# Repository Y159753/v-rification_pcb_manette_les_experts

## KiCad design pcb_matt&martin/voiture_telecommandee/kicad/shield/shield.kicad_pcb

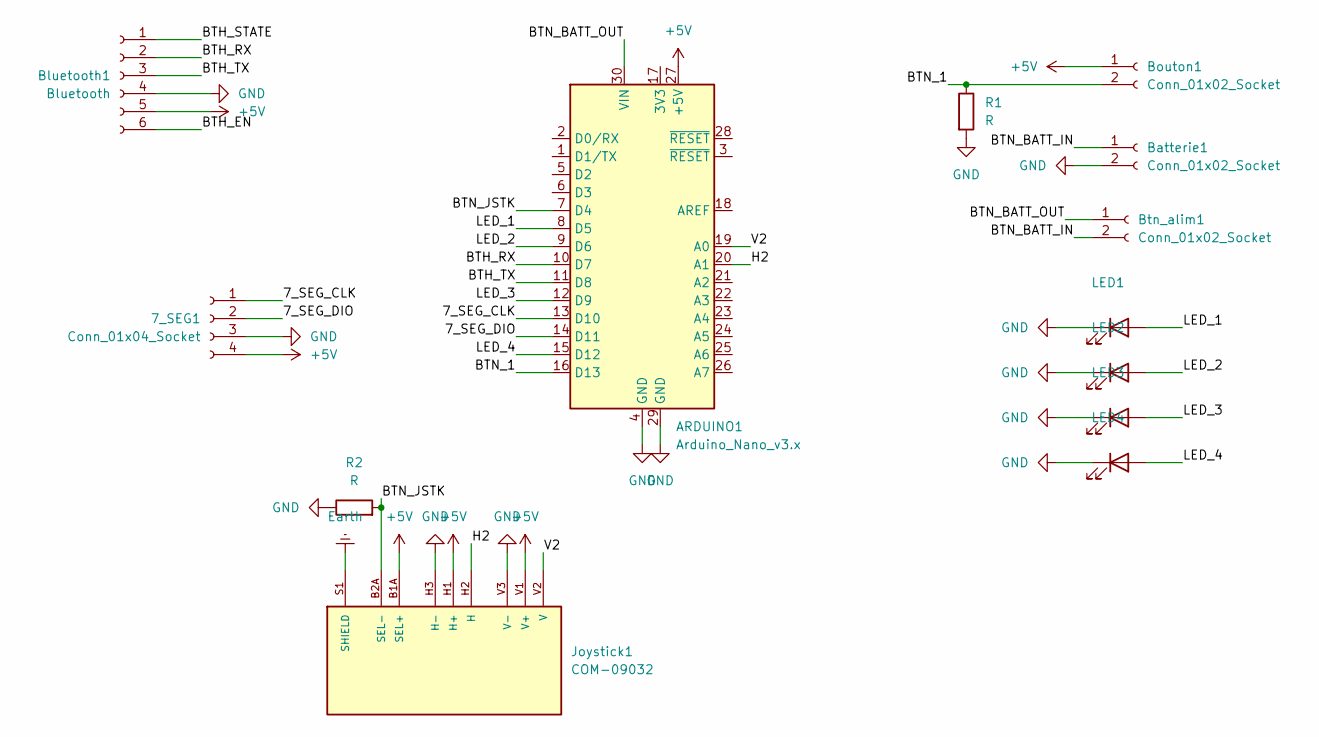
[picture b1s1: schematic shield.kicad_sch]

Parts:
7_SEG1: Conn_01x04_Socket; PinSocket_1x04_P2.54mm_Vertical
ARDUINO1: Arduino_Nano_v3.x; Arduino_Nano
Batterie1: Conn_01x02_Socket; JST_XH_B2B-XH-A_1x02_P2.50mm_Vertical
Bluetooth1: Bluetooth; PinSocket_1x06_P2.54mm_Horizontal
Bouton1: Conn_01x02_Socket; JST_XH_B2B-XH-A_1x02_P2.50mm_Vertical
Btn_alim1: Conn_01x02_Socket; JST_XH_B2B-XH-A_1x02_P2.50mm_Vertical
Joystick1: COM-09032; XDCR_COM-09032; PARTREV N/A
LED1, LED2, LED3, LED4: LED; LED_D5.0mm_Clear
R1, R2: R; R_Axial_DIN0207_L6.3mm_D2.5mm_P10.16mm_Horizontal

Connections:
+5V: 7_SEG1.4, ARDUINO1.27 (+5V), Bluetooth1.5, Bouton1.1, Joystick1.B1A (SEL+), Joystick1.H1 (H+), Joystick1.V1 (V+)
/7_SEG_CLK: 7_SEG1.1, ARDUINO1.13 (D10)
/7_SEG_DIO: 7_SEG1.2, ARDUINO1.14 (D11)
/<NO NET>: ARDUINO1.7 (D4), Joystick1.B2A (SEL-), R2.2
/BTH_EN: Bluetooth1.6
/BTH_RX: ARDUINO1.10 (D7), Bluetooth1.2
/BTH_STATE: Bluetooth1.1
/BTH_TX: ARDUINO1.11 (D8), Bluetooth1.3
/BTN_1: ARDUINO1.16 (D13), Bouton1.2, R1.1
/BTN_BATT_IN: Batterie1.1, Btn_alim1.2
/BTN_BATT_OUT: ARDUINO1.30 (VIN), Btn_alim1.1
/H2: ARDUINO1.20 (A1), Joystick1.H2 (H)
/LED_1: ARDUINO1.8 (D5), LED1.2 (A)
/LED_2: ARDUINO1.9 (D6), LED2.2 (A)
/LED_3: ARDUINO1.12 (D9), LED3.2 (A)
/LED_4: ARDUINO1.15 (D12), LED4.2 (A)
/V2: ARDUINO1.19 (A0), Joystick1.V2 (V)
Earth: Joystick1.S1 (SHIELD), Joystick1.S2 (SHIELD), Joystick1.S3 (SHIELD), Joystick1.S4 (SHIELD)
GND: 7_SEG1.3, ARDUINO1.4 (GND), ARDUINO1.29 (GND), Batterie1.2, Bluetooth1.4, Joystick1.H3 (H-), Joystick1.V3 (V-), LED1.1 (K), LED2.1 (K), LED3.1 (K), LED4.1 (K), R1.2, R2.1

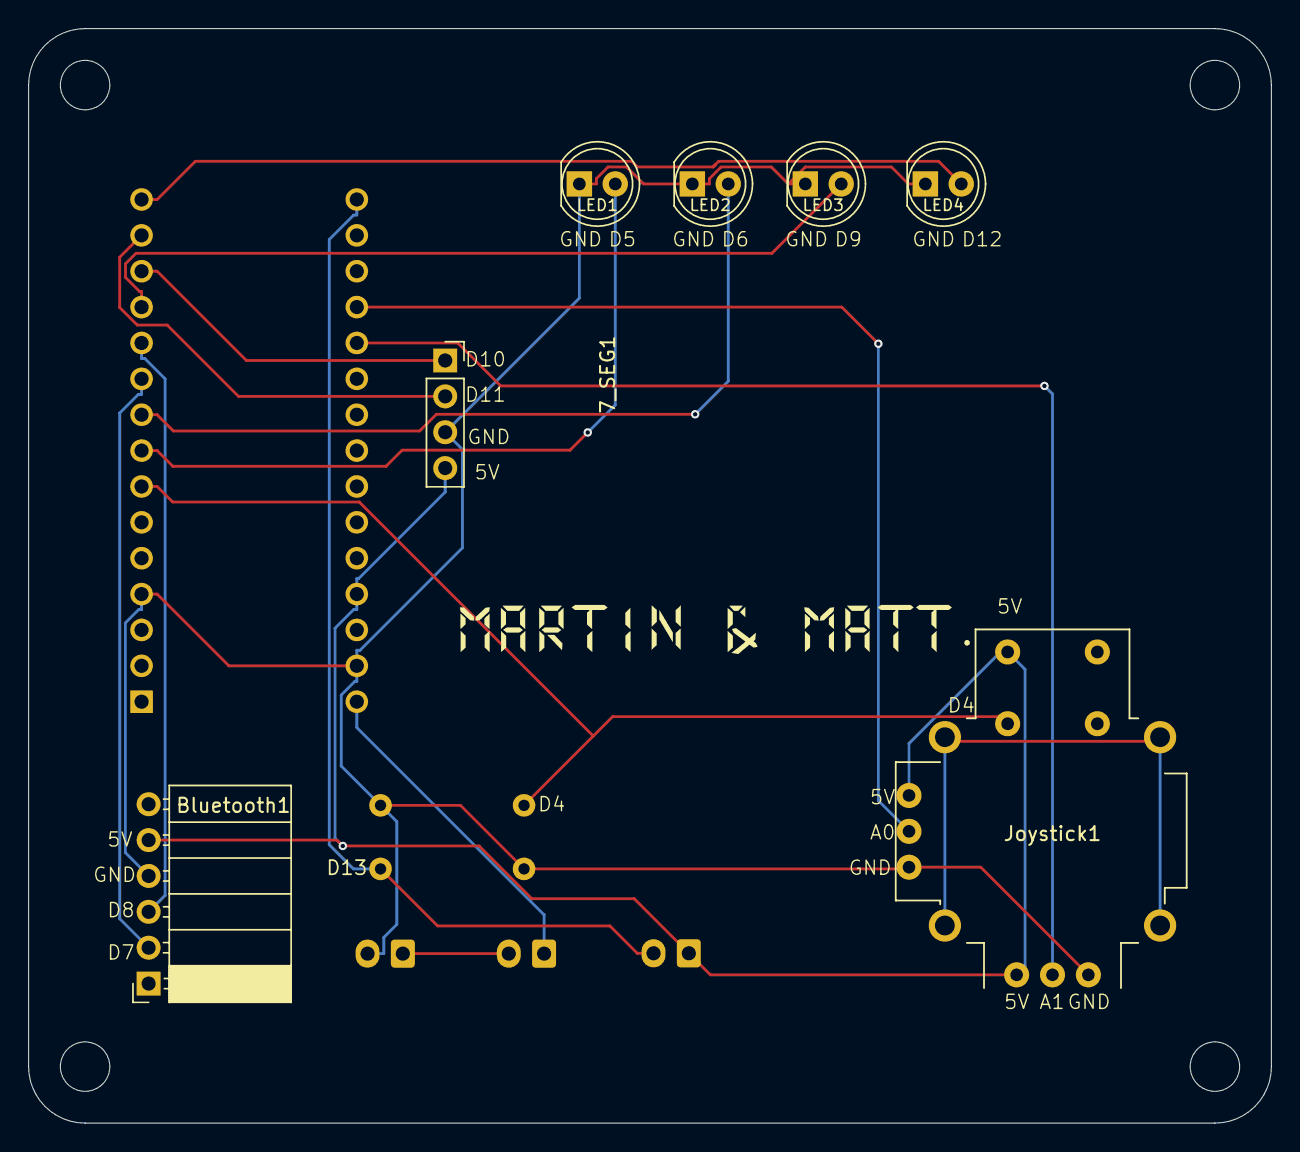
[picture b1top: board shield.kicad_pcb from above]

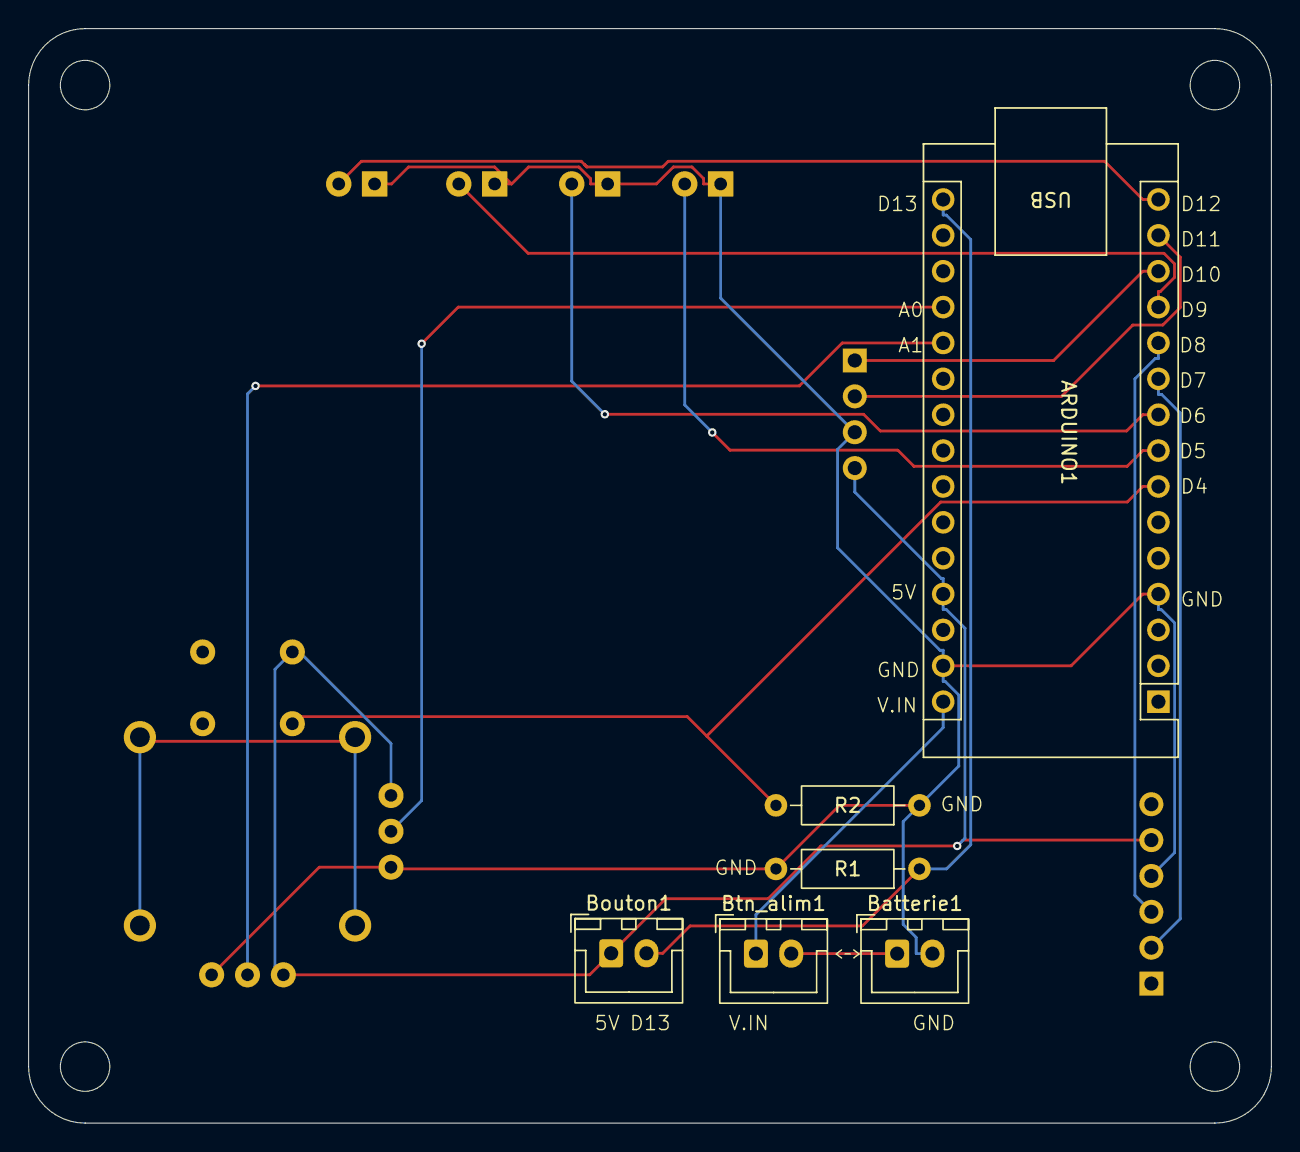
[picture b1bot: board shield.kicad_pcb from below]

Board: 2 copper layers, 88.0 x 77.5 mm, 13 parts (6 on the bottom side), 17 nets.

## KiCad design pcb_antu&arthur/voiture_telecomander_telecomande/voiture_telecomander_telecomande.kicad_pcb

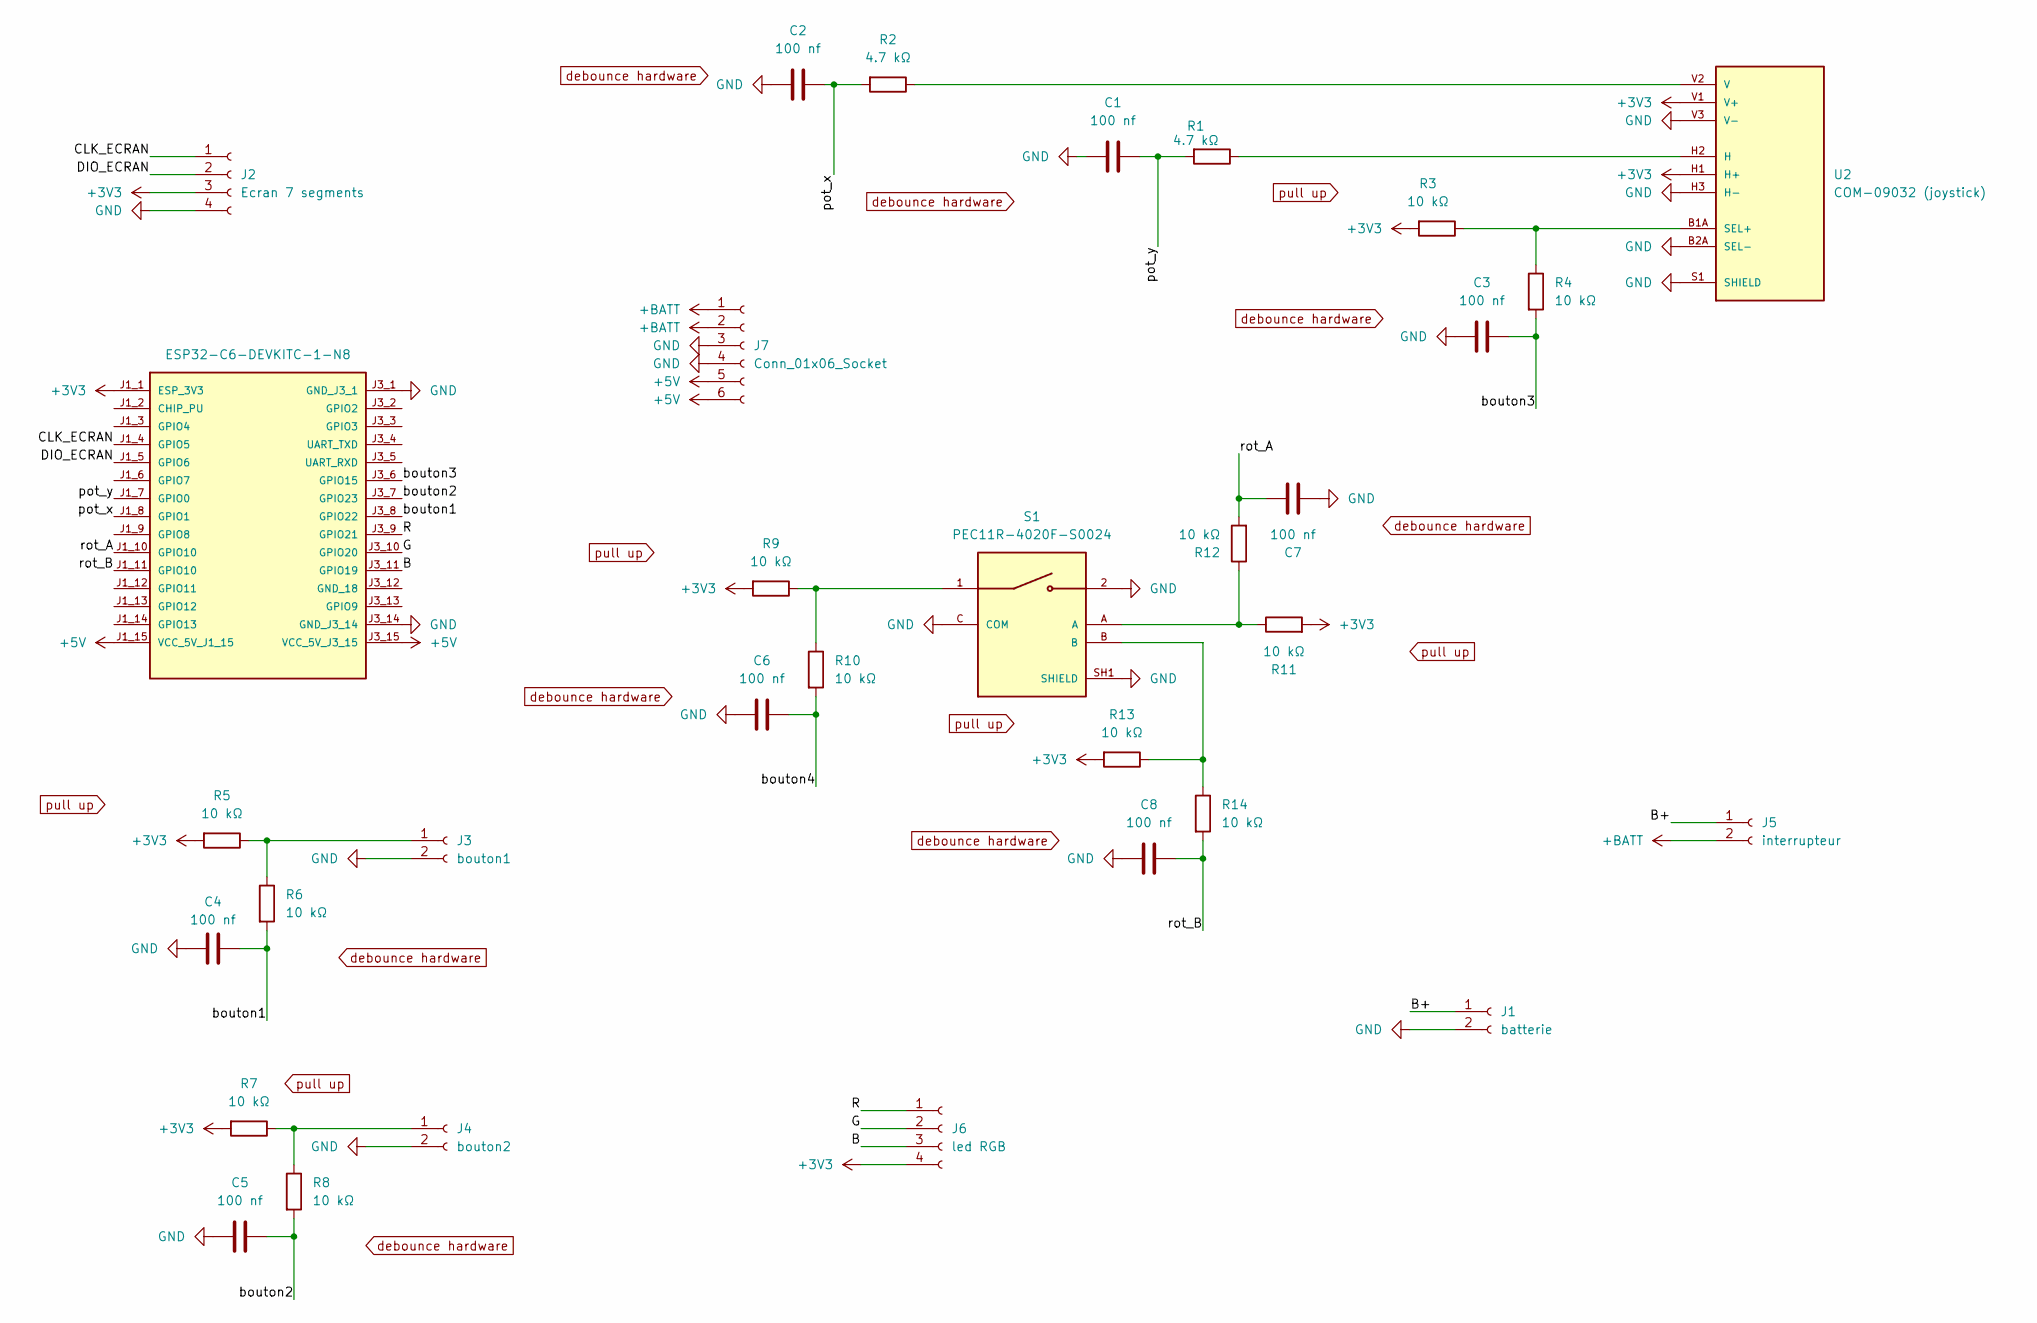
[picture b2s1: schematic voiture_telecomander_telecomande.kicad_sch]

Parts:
C1, C2, C3, C4, C5, C6, C7, C8: 100 nf; C_Radial_D4.0mm_H7.0mm_P1.50mm
J1: batterie; JST_XH_B2B-XH-A_1x02_P2.50mm_Vertical
J2: Ecran 7 segments; PinSocket_1x04_P2.54mm_Vertical
J3: bouton1; JST_XH_B2B-XH-A_1x02_P2.50mm_Vertical
J4: bouton2; JST_XH_B2B-XH-A_1x02_P2.50mm_Vertical
J5: interrupteur; JST_XH_B2B-XH-A_1x02_P2.50mm_Vertical
J6: led RGB; PinSocket_1x04_P2.54mm_Vertical
J7: Conn_01x06_Socket; PinSocket_1x06_P2.54mm_Vertical
R1, R2: 4.7 kΩ; R_Axial_DIN0207_L6.3mm_D2.5mm_P10.16mm_Horizontal
R3, R4, R5, R6, R7, R8, R9, R10, R11, R12, R13, R14: 10 kΩ; R_Axial_DIN0207_L6.3mm_D2.5mm_P10.16mm_Horizontal
S1: PEC11R-4020F-S0024; XDCR_PEC11R-4020F-S0024; PARTREV 11/23
U1: ESP32-C6-DEVKITC-1-N8; MODULE_ESP32-C6-DEVKITC-1-N8; PARTREV 1.3
U2: COM-09032 (joystick); XDCR_COM-09032; PARTREV N/A

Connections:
+3V3: J2.3, J6.4, R3.2, R5.2, R7.2, R9.2, R11.2, R13.2, U1.J1_1 (ESP_3V3), U2.H1 (H+), U2.V1 (V+)
+5V: J7.5, J7.6, U1.J1_15 (VCC_5V_J1_15), U1.J3_15 (VCC_5V_J3_15)
+BATT: J5.2, J7.1, J7.2
/B: J6.3, U1.J3_11 (GPIO19)
/B+: J1.1, J5.1
/CLK_ECRAN: J2.1, U1.J1_4 (GPIO5)
/DIO_ECRAN: J2.2, U1.J1_5 (GPIO6)
/G: J6.2, U1.J3_10 (GPIO20)
/R: J6.1, U1.J3_9 (GPIO21)
/bouton1: C4.2, R6.2, U1.J3_8 (GPIO22)
/bouton2: C5.2, R8.2, U1.J3_7 (GPIO23)
/bouton3: C3.2, R4.2, U1.J3_6 (GPIO15)
/bouton4: C6.2, R10.2
/pot_x: C2.2, R2.2, U1.J1_8 (GPIO1)
/pot_y: C1.2, R1.2, U1.J1_7 (GPIO0)
/rot_A: C7.2, R12.2, U1.J1_10 (GPIO10)
/rot_B: C8.2, R14.2, U1.J1_11 (GPIO10)
GND: C1.1, C2.1, C3.1, C4.1, C5.1, C6.1, C7.1, C8.1, J1.2, J2.4, J3.2, J4.2, J7.3, J7.4, S1.2, S1.C (COM), S1.SH1 (SHIELD), S1.SH2 (SHIELD), U1.J3_1 (GND_J3_1), U1.J3_14 (GND_J3_14), U2.B2A (SEL-), U2.H3 (H-), U2.S1 (SHIELD), U2.S2 (SHIELD), U2.S3 (SHIELD), U2.S4 (SHIELD), U2.V3 (V-)
unnamed: J3.1, R5.1, R6.1
unnamed: J4.1, R7.1, R8.1
unnamed: R9.1, R10.1, S1.1
unnamed: R11.1, R12.1, S1.A
unnamed: R13.1, R14.1, S1.B
unnamed: R1.1, U2.H2 (H)
unnamed: R3.1, R4.1, U2.B1A (SEL+)
unnamed: R2.1, U2.V2 (V)

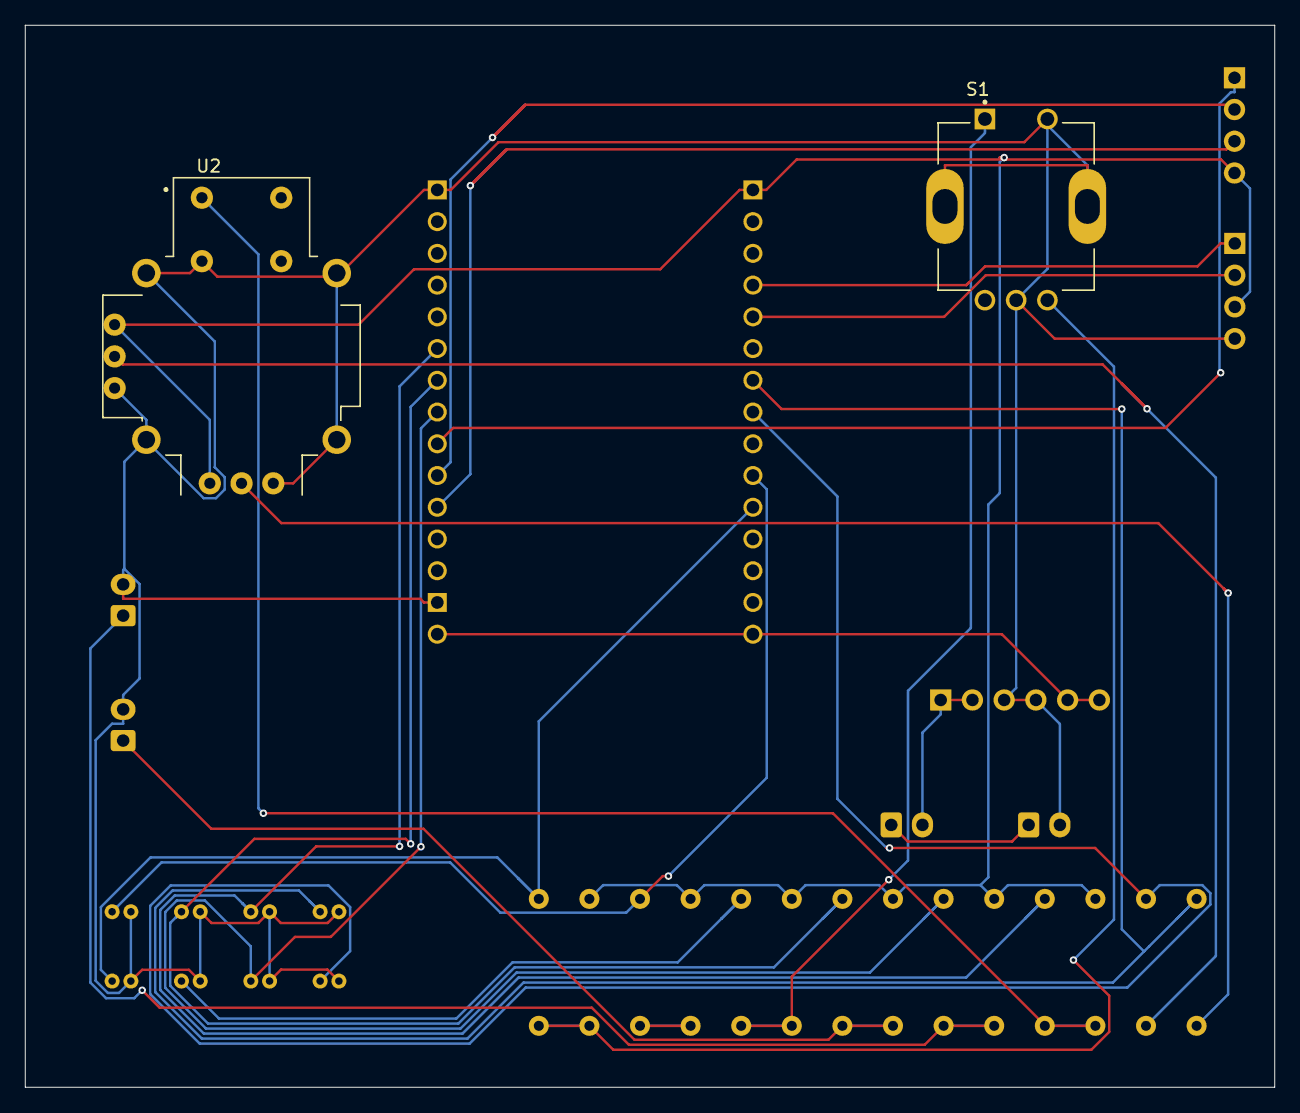
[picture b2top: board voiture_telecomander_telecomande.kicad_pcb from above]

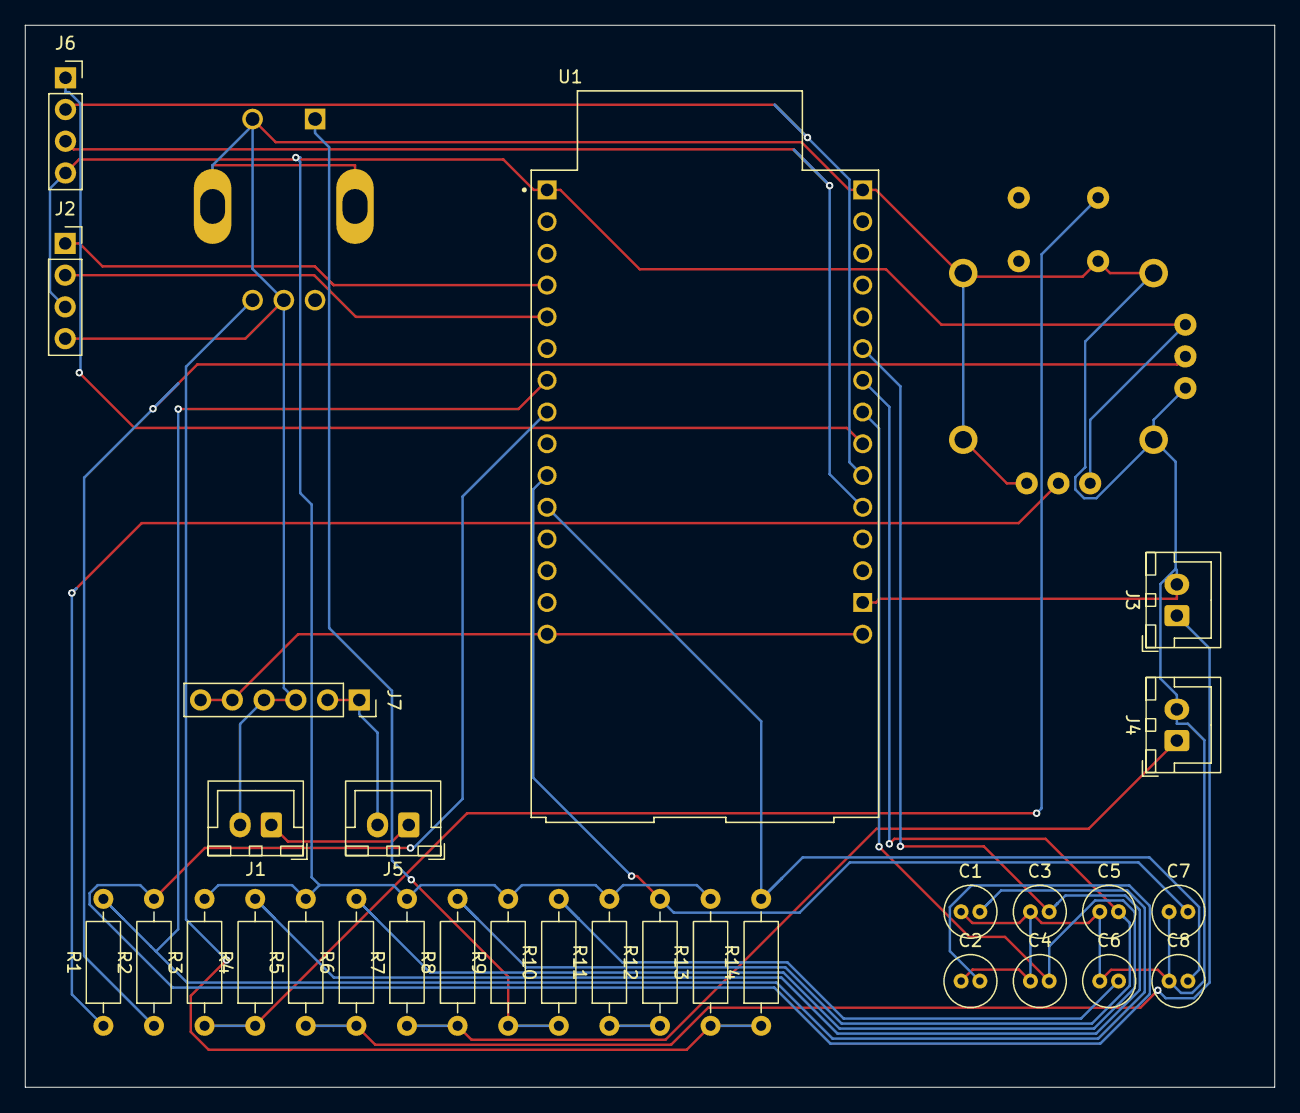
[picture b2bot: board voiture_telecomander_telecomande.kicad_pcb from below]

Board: 2 copper layers, 100.0 x 85.0 mm, 32 parts (30 on the bottom side), 26 nets.

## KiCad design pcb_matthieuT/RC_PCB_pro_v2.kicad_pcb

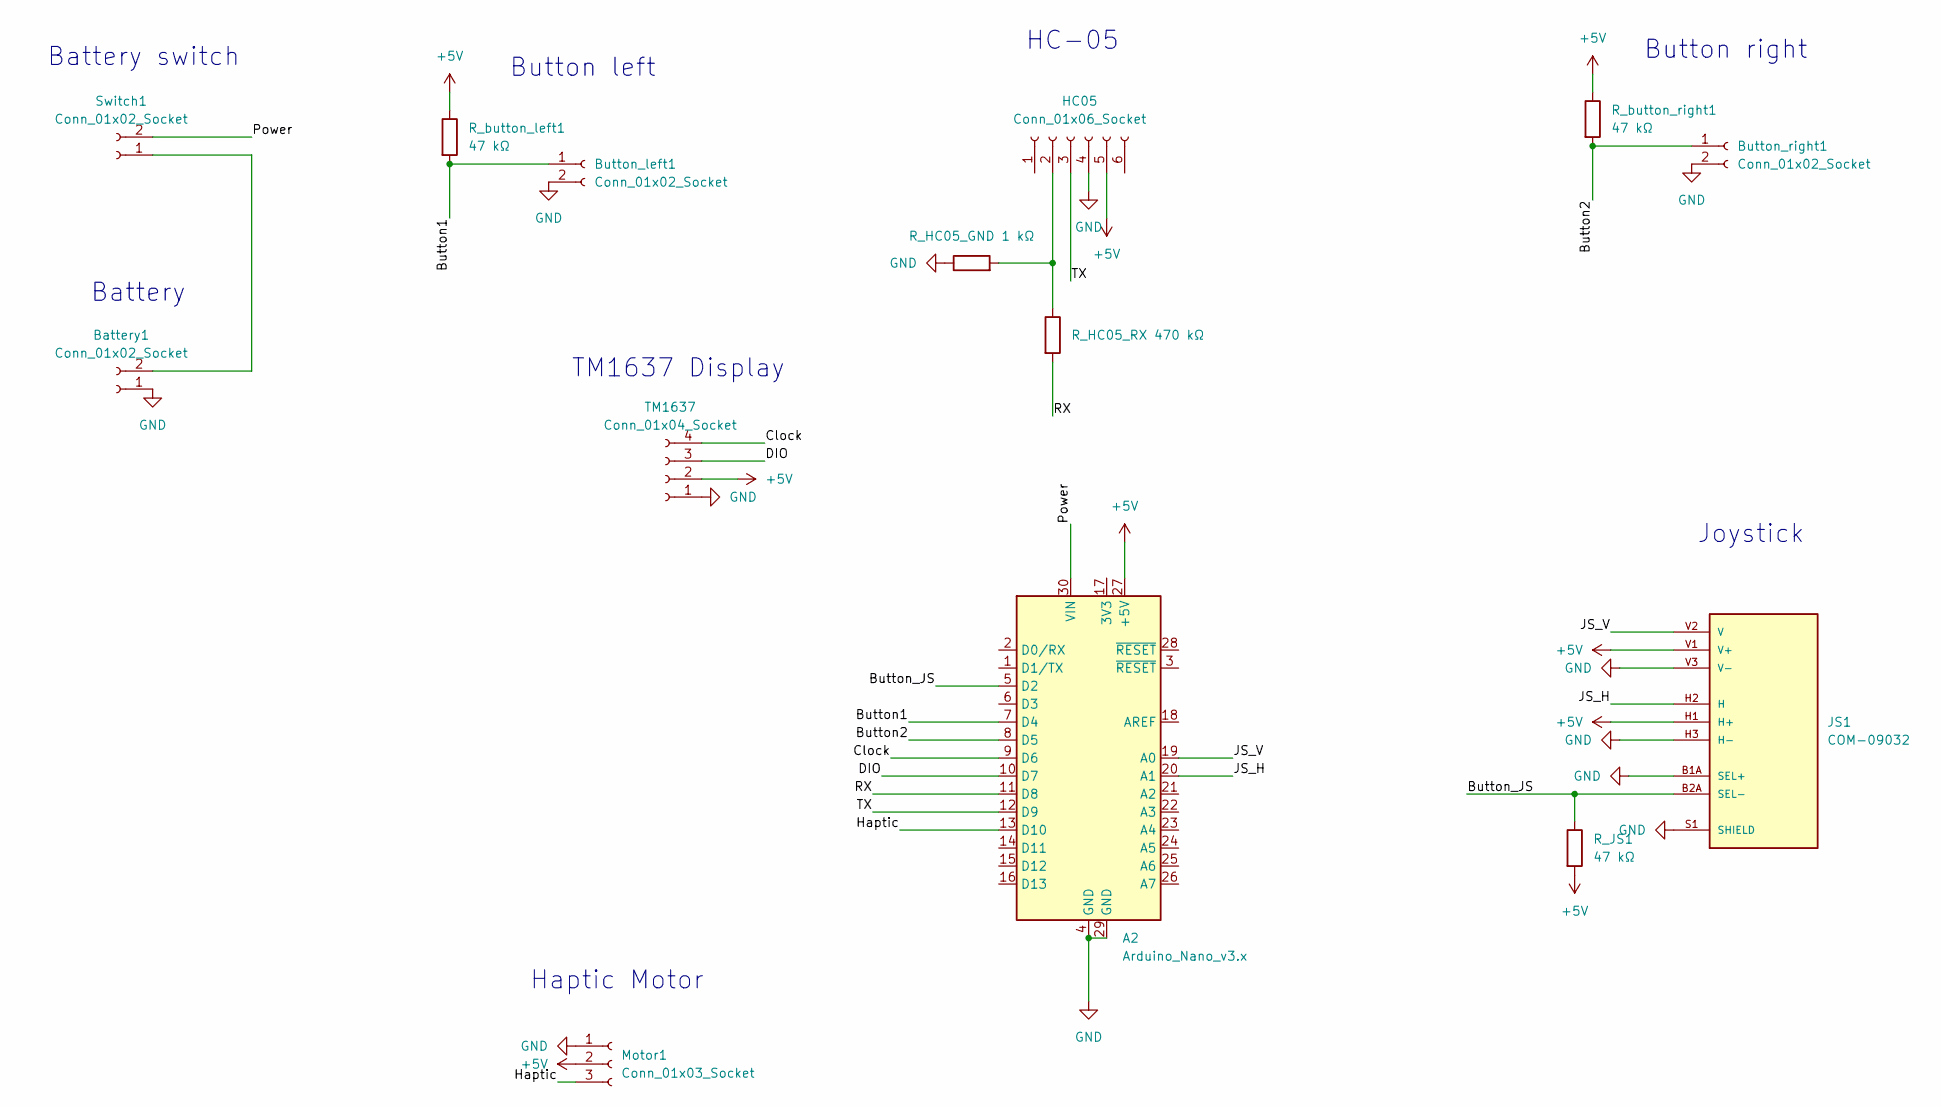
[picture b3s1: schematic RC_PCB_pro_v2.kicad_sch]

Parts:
A2: Arduino_Nano_v3.x; Arduino_Nano
Battery1: Conn_01x02_Socket; JST_XH_B2B-XH-A_1x02_P2.50mm_Vertical
Button_left1: Conn_01x02_Socket; JST_XH_B2B-XH-A_1x02_P2.50mm_Vertical
Button_right1: Conn_01x02_Socket; JST_XH_B2B-XH-A_1x02_P2.50mm_Vertical
HC05: Conn_01x06_Socket; PinSocket_1x06_P2.54mm_Horizontal
JS1: COM-09032; XDCR_COM-09032; PARTREV N/A
Motor1: Conn_01x03_Socket; PinSocket_1x03_P2.00mm_Horizontal
R1: R_HC05_RX 470 kΩ; R_Axial_DIN0207_L6.3mm_D2.5mm_P10.16mm_Horizontal
R2: R_HC05_GND 1 kΩ; R_Axial_DIN0207_L6.3mm_D2.5mm_P10.16mm_Horizontal
R_JS1: 47 kΩ; R_Axial_DIN0207_L6.3mm_D2.5mm_P10.16mm_Horizontal
R_button_left1: 47 kΩ; R_Axial_DIN0207_L6.3mm_D2.5mm_P10.16mm_Horizontal
R_button_right1: 47 kΩ; R_Axial_DIN0207_L6.3mm_D2.5mm_P10.16mm_Horizontal
Switch1: Conn_01x02_Socket; JST_XH_B2B-XH-A_1x02_P2.50mm_Vertical
TM1637: Conn_01x04_Socket; PinSocket_1x04_P2.54mm_Vertical

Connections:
+5V: A2.27 (+5V), HC05.5, JS1.H1 (H+), JS1.V1 (V+), Motor1.2, R_JS1.2, R_button_left1.1, R_button_right1.1, TM1637.2
/Button1: A2.7 (D4), Button_left1.1, R_button_left1.2
/Button2: A2.8 (D5), Button_right1.1, R_button_right1.2
/Button_JS: A2.5 (D2), JS1.B2A (SEL-), R_JS1.1
/Clock: A2.9 (D6), TM1637.4
/DIO: A2.10 (D7), TM1637.3
/Haptic: A2.13 (D10), Motor1.3
/JS_H: A2.20 (A1), JS1.H2 (H)
/JS_V: A2.19 (A0), JS1.V2 (V)
/Power: A2.30 (VIN), Switch1.2
/RX: A2.11 (D8), R1.2
/TX: A2.12 (D9), HC05.3
GND: A2.4 (GND), A2.29 (GND), Battery1.1, Button_left1.2, Button_right1.2, HC05.4, JS1.B1A (SEL+), JS1.H3 (H-), JS1.S1 (SHIELD), JS1.S2 (SHIELD), JS1.S3 (SHIELD), JS1.S4 (SHIELD), JS1.V3 (V-), Motor1.1, R2.1, TM1637.1
unnamed: Battery1.2, Switch1.1
unnamed: HC05.2, R1.1, R2.2

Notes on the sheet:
Battery
Battery switch
TM1637 Display
Button right
HC-05
Joystick
Haptic Motor
Button left

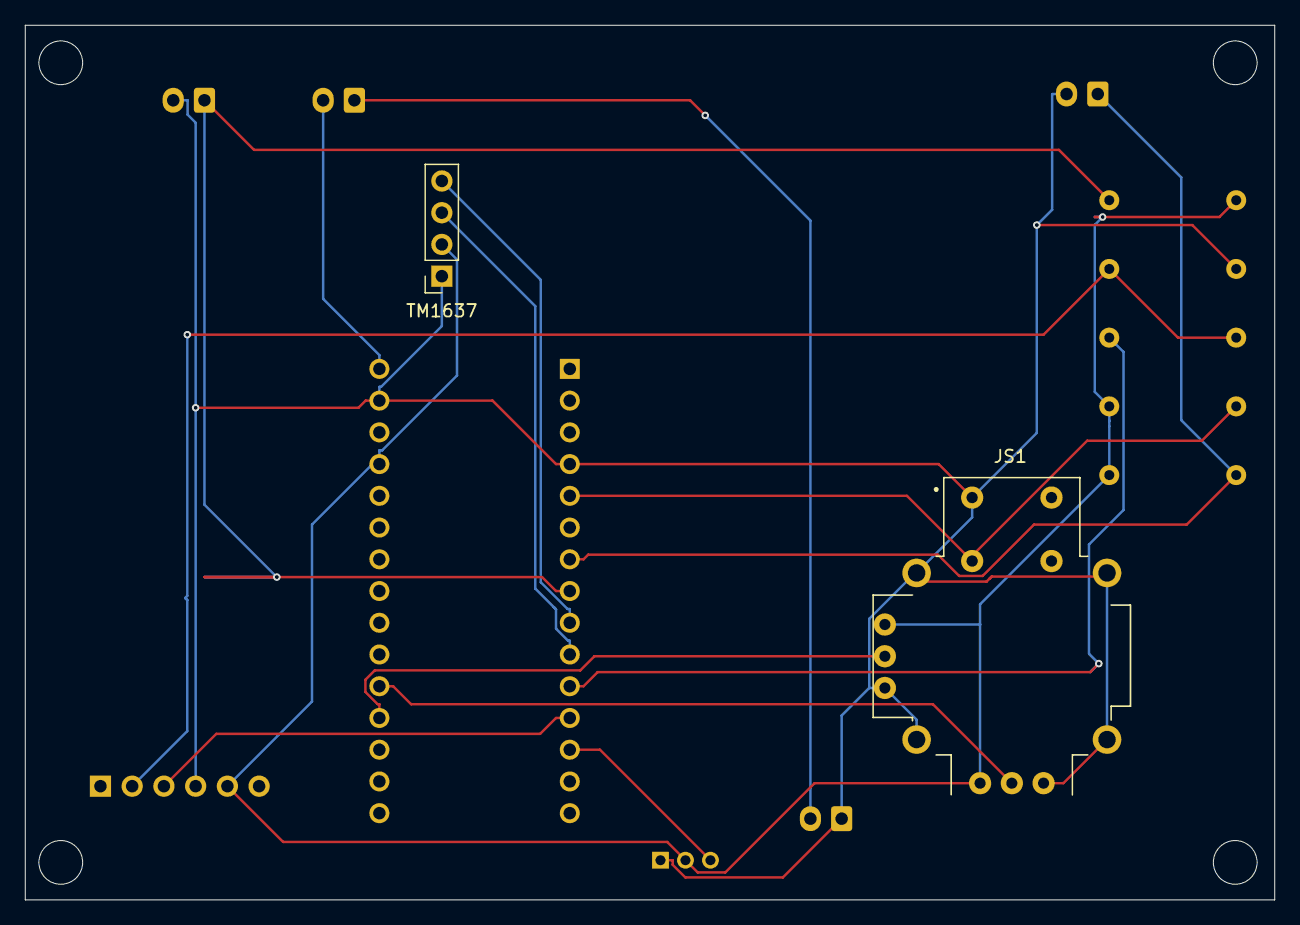
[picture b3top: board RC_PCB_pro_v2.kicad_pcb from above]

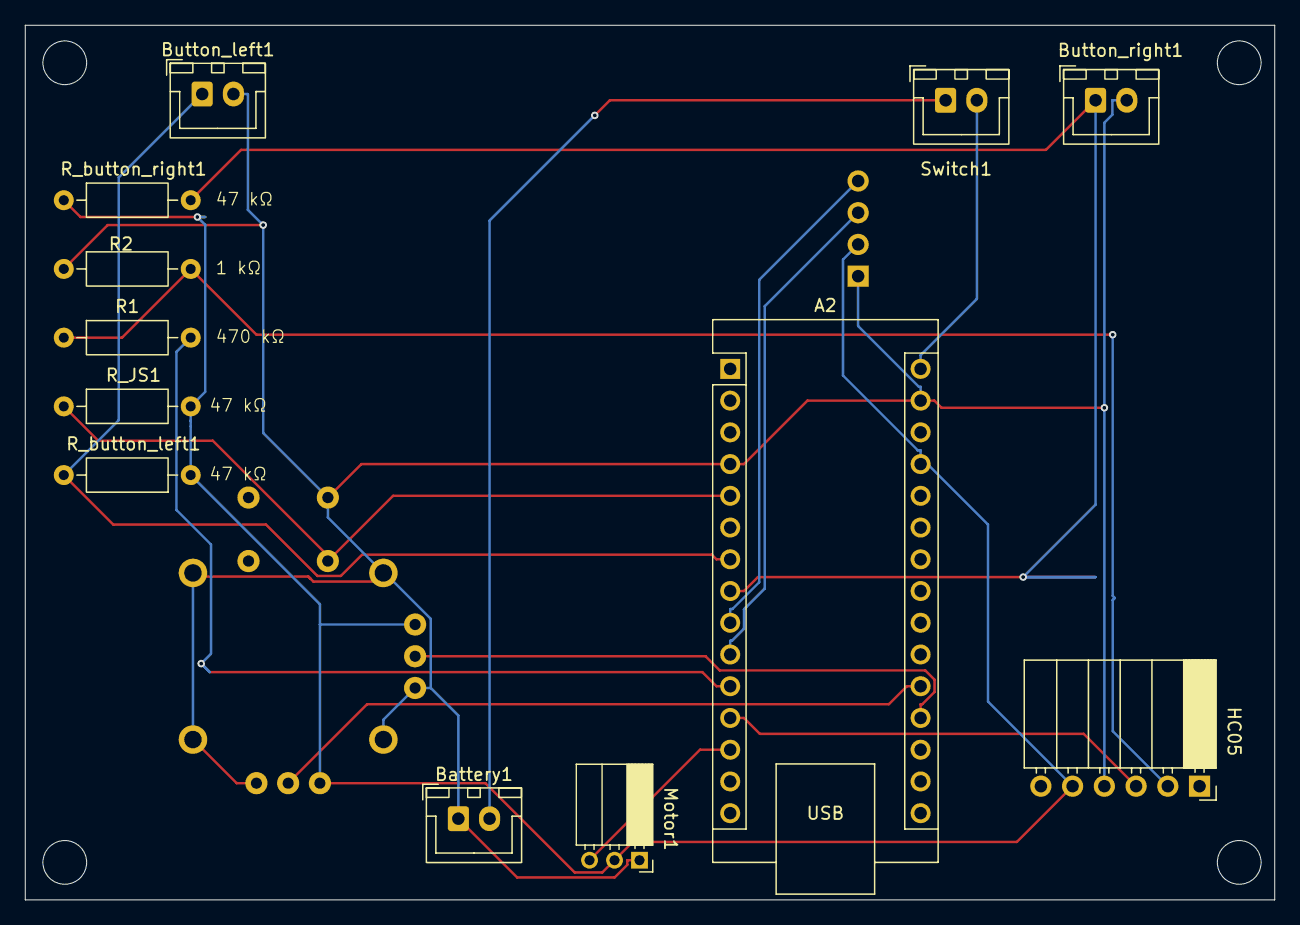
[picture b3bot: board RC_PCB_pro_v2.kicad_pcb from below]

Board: 2 copper layers, 100.0 x 70.0 mm, 14 parts (12 on the bottom side), 15 nets.

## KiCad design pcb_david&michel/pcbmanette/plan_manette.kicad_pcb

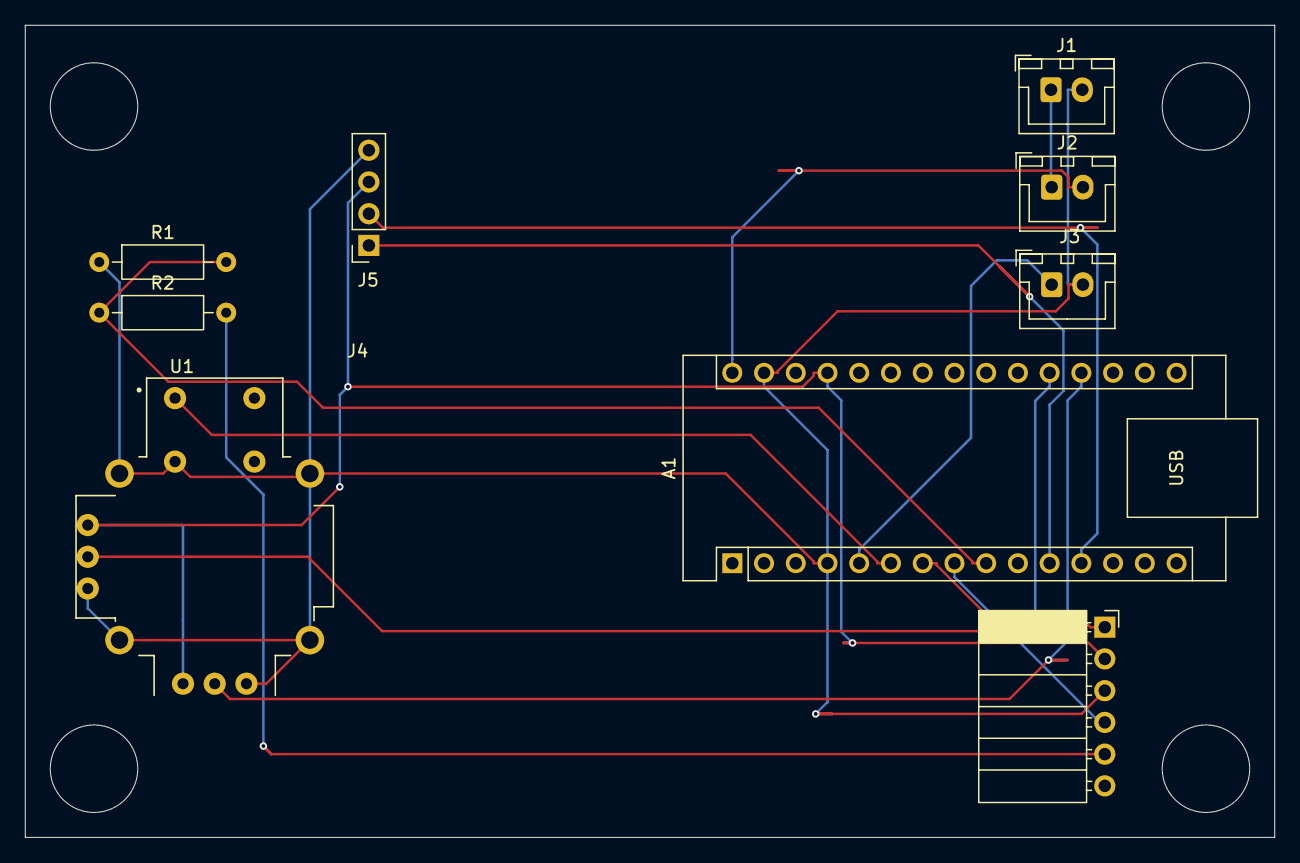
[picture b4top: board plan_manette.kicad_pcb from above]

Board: 2 copper layers, 100.0 x 65.0 mm, 9 parts (0 on the bottom side), 14 nets.

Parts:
A1: Arduino_Nano_v3.x; Arduino_Nano
J1: batterie; JST_XH_B2B-XH-A_1x02_P2.50mm_Vertical
J2: interrupteur; JST_XH_B2B-XH-A_1x02_P2.50mm_Vertical
J3: bouton déporté; JST_XH_B2B-XH-A_1x02_P2.50mm_Vertical
J4: Module Bluetooth; PinSocket_1x06_P2.54mm_Horizontal
J5: Ecran 7 segments; PinSocket_1x04_P2.54mm_Vertical
R1, R2: R; R_Axial_DIN0207_L6.3mm_D2.5mm_P10.16mm_Horizontal
U1: COM-09032; XDCR_COM-09032

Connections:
+5V: A1.27 (+5V), J4.2, J5.3, U1.H1 (H+), U1.V1 (V+)
+9V: J1.1, J2.1
/9V_APRES_INTERRUPTEUR: A1.30 (VIN), J2.2
/CLK_ECRAN: A1.11 (D8), J5.1
/DEPORT_BOUTON: A1.5 (D2), J3.1
/DIO_ECRAN: A1.12 (D9), J5.2
/EN_BLUE: A1.7 (D4), J4.1
/POT_BOUTON: A1.6 (D3), U1.B1A (SEL+)
/POT_HORIZONTAL: A1.19 (A0), U1.H2 (H)
/POT_VERTICAL: A1.20 (A1), U1.V2 (V)
/RXD_BLUE: J4.5, R2.2
/TXD_BLUE: A1.8 (D5), J4.4
GND: A1.4 (GND), A1.29 (GND), J1.2, J3.2, J4.3, J5.4, R1.1, U1.B2A (SEL-), U1.H3 (H-), U1.S1 (SHIELD), U1.S2 (SHIELD), U1.S3 (SHIELD), U1.S4 (SHIELD), U1.V3 (V-)
unnamed: A1.9 (D6), R1.2, R2.1

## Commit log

2026-02-13 correction
2026-02-14 Ajouté zip kicad
    J'ai tout mis dans un zip, j'espere que c'est pas grave
2026-02-16 Remote controller
2026-02-16 Envoi PCB [Louis & Wassim]
    J'ai zippé mon dossier. Vous pourriez me dire si vous avez tout bien reçu ?
2026-02-16 Organisation du dossier
2026-02-16 File dezippé
2026-02-17 Forgotten files
2026-02-18 pcb arthur et antu
2026-02-18 Reorganisation des fichiers
    Réorganisé les fichiers notamment enlevé le zip inutile
2026-02-18 Résolu Issue #12
    J'ai tout simplement mis le symbole sur l'Arduino et rerouté et tout le tralala
2026-02-18 Résolution de l'issue #11
    Pas sûr-sûr que fallait faire comme ça mais bon (https://github.com/Y159753/v-rification_pcb_manette_les_experts/issues/11#issuecomment-3921551236) Donc du coup j'ai mis le signe gnd sur la 2eme broc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
2026-02-18 changement de +5v à Alim_ESP
2026-02-18 Ajout fichiers dézippés Michel / David
2026-02-19 Schematic and D real estate corrections
2026-02-21 supprime les backups dans pcb_antu&arthur
2026-02-21 changement purement estetique dans le schema pour une meileur compréhension
2026-02-25 Déplacement à partir du dossier d'origine
2026-03-09 ajout de 2 modeles 3d -esp32-c6 -encodeur rotatif
2026-03-09 ajout du model 3D du joystick
2026-03-10 mise a jour 3d
2026-03-10 mise a jour des 3d maintenant les modeles 3d sont dans le projet et non plus externe
2026-03-11 mise a jour PCB antu_arthur
2026-03-11 ajout d'un converter buck
2026-03-11 Remote PCB V2
2026-03-11 ajout de modeles 3d -7 segment
2026-03-18 déplacement composant
2026-03-18 deplacement footprint
2026-03-18 mise a jour pcb enleve le model du 7segment
2026-04-02 bon euuuuu y'a bcp de changements
